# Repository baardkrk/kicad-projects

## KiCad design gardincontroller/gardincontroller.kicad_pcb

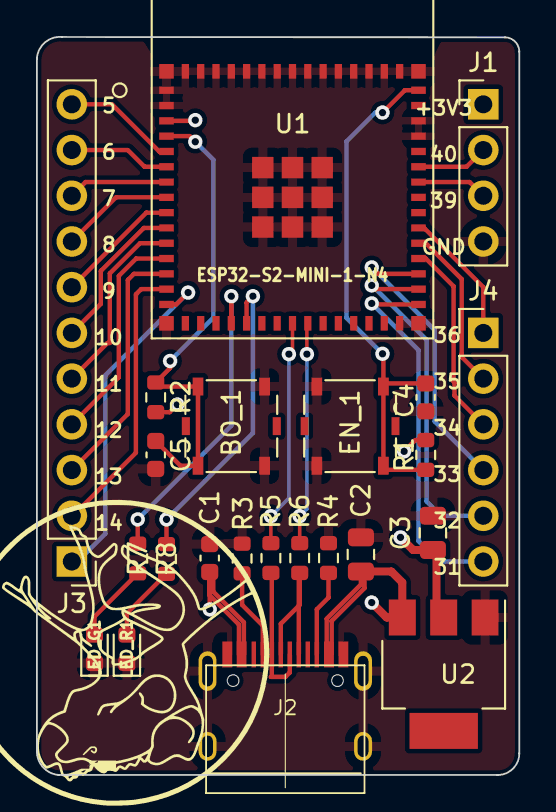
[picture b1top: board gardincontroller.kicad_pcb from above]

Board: 2 copper layers, 26.8 x 41.0 mm, 23 parts (0 on the bottom side), 34 nets.

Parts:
BO_1: SW_Push; SW_SPST_Panasonic_EVQPL_3PL_5PL_PT_A08
C1, C4, C5: 0.1uf; C_0603_1608Metric
C2, C3: 10uf; C_0805_2012Metric
EN_1: SW_Push; SW_SPST_Panasonic_EVQPL_3PL_5PL_PT_A08
J1: Conn_01x04_Male; PinHeader_1x04_P2.54mm_Vertical
J2: USB_C_Receptacle_USB2.0; TYPE-C-31-M-12
J3: Conn_01x10_Male; PinHeader_1x11_P2.54mm_Vertical
J4: Conn_01x06_Male; PinHeader_1x06_P2.54mm_Vertical
LED_G1: LED; LED_0603_1608Metric
LED_R1: LED; LED_0603_1608Metric
R1, R2: 10k; R_0603_1608Metric
R3, R4: 5.1k; R_0603_1608Metric
R5, R6: 33R; R_0603_1608Metric
R7: 45R; R_0603_1608Metric
R8: 55R; R_0603_1608Metric
U1: ESP32-S2-MINI-1-N4
U2: LM1117-3.3; SOT-223

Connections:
+3V3: C3.1, J1.1, R1.2, R2.2, U1.3 (3V3), U2.2 (VO)
+5V: C1.1, C2.1, J2.A4 (VBUS), J2.A9 (VBUS), J2.B4 (VBUS), J2.B9 (VBUS), U2.3 (VI)
/BOOT: BO_1.2, C5.2, R2.1, U1.4 (IO0)
/ENABLE: C4.2, EN_1.2, R1.1, U1.45 (EN)
GND: BO_1.1, C1.2, C2.2, C3.2, C4.1, C5.1, EN_1.1, J1.4, J2.A1 (GND), J2.A12 (GND), J2.B1 (GND), J2.B12 (GND), J2.S1 (SHIELD), LED_G1.1 (K), LED_R1.1 (K), R3.1, R4.1, U1.1 (GND), U1.2 (GND), U1.30 (GND), U1.42 (GND), U1.43 (GND), U1.46 (GND), U1.47 (GND), U1.48 (GND), U1.49 (GND), U1.50 (GND), U1.51 (GND), U1.52 (GND), U1.53 (GND), U1.54 (GND), U1.55 (GND), U1.56 (GND), U1.57 (GND), U1.58 (GND), U1.59 (GND), U1.60 (GND), U1.61 (GND), U1.62 (GND), U1.63 (GND), U1.64 (GND), U1.65 (GND), U1.66 (GND), U1.67 (GND), U1.68 (GND), U1.69 (GND), U1.70 (GND), U1.71 (GND), U1.72 (GND), U1.73 (GND), U2.1 (GND)
unnamed: J1.2, U1.40 (RXD0)
unnamed: J1.3, U1.39 (TXD0)
unnamed: J2.A5 (CC1), R3.2
unnamed: J2.A6 (D+), J2.B6 (D+), R6.2
unnamed: J2.A7 (D-), J2.B7 (D-), R5.2
unnamed: J2.B5 (CC2), R4.2
unnamed: J3.1, U1.15 (IO11)
unnamed: LED_G1.2 (A), R7.2
unnamed: LED_R1.2 (A), R8.2
unnamed: J3.11, U1.5 (IO1)
unnamed: J3.10, U1.6 (IO2)
unnamed: J3.9, U1.7 (IO3)
unnamed: J3.8, U1.8 (IO4)
unnamed: J3.7, U1.9 (IO5)
unnamed: J3.6, U1.10 (IO6)
unnamed: J3.5, U1.11 (IO7)
unnamed: J3.4, U1.12 (IO8)
unnamed: J3.3, U1.13 (IO9)
unnamed: J3.2, U1.14 (IO10)
unnamed: R7.1, U1.19 (IO15)
unnamed: R8.1, U1.20 (IO16)
unnamed: J4.6, U1.31 (IO35)
unnamed: J4.5, U1.32 (IO36)
unnamed: J4.4, U1.33 (IO37)
unnamed: J4.3, U1.34 (IO38)
unnamed: J4.2, U1.35 (IO39)
unnamed: J4.1, U1.36 (IO40)
USB_N: R5.1, U1.23 (IO19)
USB_P: R6.1, U1.24 (IO20)

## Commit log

2022-03-27 Fixet løse ledninger
2022-03-27 flyttet ledning
2022-03-27 11 pin header istedet
2022-03-27 fikset et par ledninger

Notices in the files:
parts and their libraries:
Copyright 2021 Accelerated Designs. All rights reserved.
